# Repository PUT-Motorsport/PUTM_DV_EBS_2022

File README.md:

# PUTM_DV_EBS_2022
A KiCad schematic and PCB project of the Emergency Brake System circuit board.

NOTE: PCB project will be updated to match EBS_1.2 scheme.

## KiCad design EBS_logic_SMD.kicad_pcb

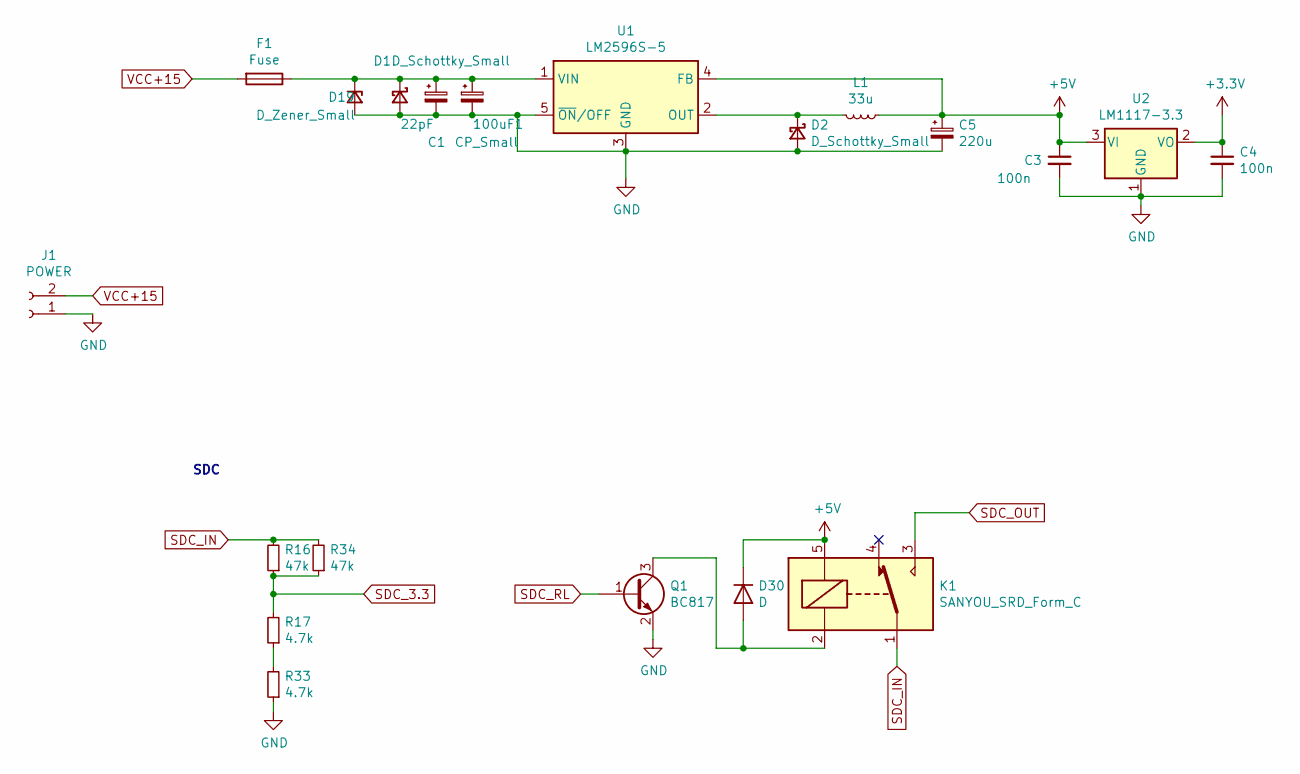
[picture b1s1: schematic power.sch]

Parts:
100uF1: CP_Small; C_1206_3216Metric
C1: 22pF; CP_Elec_6.3x5.8
C3, C4: 100n; C_1206_3216Metric
C5: 220u; CP_Elec_6.3x5.8
D1, D2: D_Schottky_Small; D_SMB
D19: D_Zener_Small; D_SMB
D30: D; D_SMB
F1: Fuse; D_SMB
J1: POWER; Molex_Micro-Fit_3.0_43650-0200_1x02_P3.00mm_Horizontal
K1: SANYOU_SRD_Form_C; Relay_SPDT_SANYOU_SRD_Series_Form_C
L1: 33u; L_12x12mm_H8mm
Q1: BC817; SOT-23
R16, R34: 47k; R_1206_3216Metric
R17, R33: 4.7k; R_1206_3216Metric
U1: LM2596S-5; TO-263-5_TabPin3
U2: LM1117-3.3; SOT-223

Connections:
+5V: C3.1, C5.1, D30.1 (K), K1.5, L1.1, U1.4 (FB), U2.3 (VI); also elsewhere on the board
GND: 100uF1.2, C1.2, C3.2, C4.2, C5.2, D1.2 (A), D2.2 (A), D19.2 (A), J1.1, Q1.2 (E), R33.1, U1.3 (GND), U1.5 (~ON~/OFF), U2.1 (GND); also elsewhere on the board
unnamed: 100uF1.1, C1.1, D1.1 (K), D19.1 (K), F1.1, U1.1 (VIN)
unnamed: D2.1 (K), L1.2, U1.2 (OUT)
unnamed: D30.2 (A), K1.2, Q1.3 (C)
unnamed: R17.1, R33.2
SDC_3.3: R16.1, R17.2, R34.1; also elsewhere on the board
SDC_IN: K1.1, R16.2, R34.2; also elsewhere on the board
SDC_OUT: K1.3; also elsewhere on the board
SDC_RL: Q1.1 (B); also elsewhere on the board
VCC: C4.1, U2.2 (VO); also elsewhere on the board
VCC+15: F1.2, J1.2

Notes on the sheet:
SDC

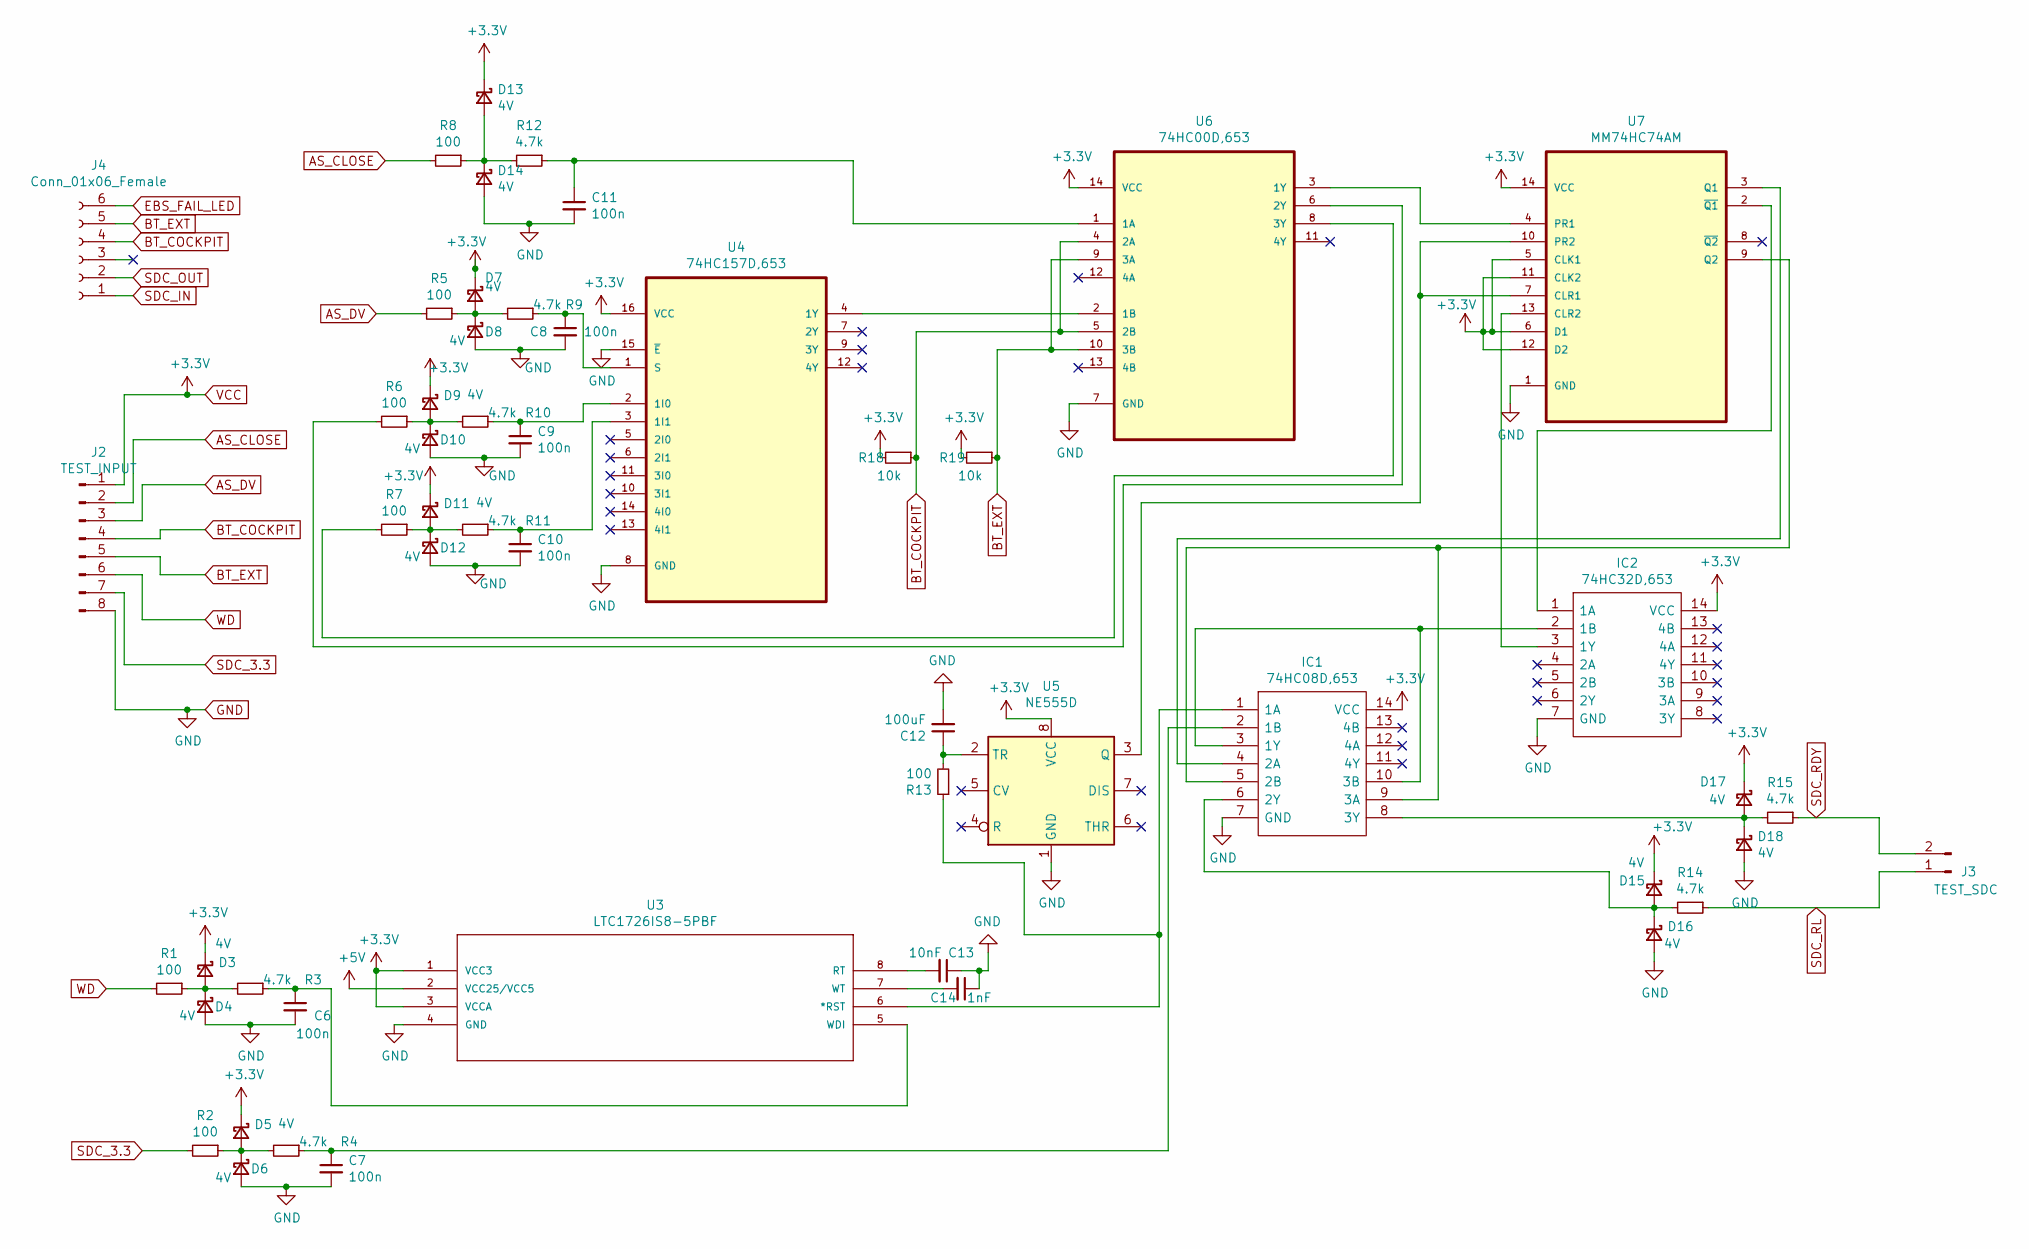
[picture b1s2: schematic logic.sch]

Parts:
C6, C7, C8, C9, C10, C11: 100n; C_1206_3216Metric
C12: 100uF; C_1206_3216Metric
C13: 10nF; C_1206_3216Metric
C14: 1nF; C_1206_3216Metric
D3, D4, D5, D6, D7, D8, D9, D10, D11, D12, D13, D14, D15, D16, D17, D18: 4V; D_SOD-323
IC1: 74HC08D,653; SOIC127P600X175-14N; Mouser Part Number 771-74HC08D-T
IC2: 74HC32D,653; SOIC127P600X175-14N; Mouser Part Number 771-74HC32D-T
J2: TEST_INPUT; PinHeader_1x08_P2.54mm_Vertical
J3: TEST_SDC; PinHeader_1x02_P2.54mm_Vertical
J4: Conn_01x06_Female; Molex_Micro-Fit_3.0_43650-0600_1x06_P3.00mm_Horizontal
R1, R2, R5, R6, R7, R8, R13: 100; R_1206_3216Metric
R3, R4, R9, R10, R11, R12, R14, R15: 4.7k; R_1206_3216Metric
R18, R19: 10k; R_1206_3216Metric
U3: LTC1726IS8-5PBF; SO-8_S; MANUFACTURER_PART_NUMBER ltc1726is85#pbf
U4: 74HC157D,653; SOIC127P600X175-16N; MPN 74HC157D,653
U5: NE555D; SOIC-8_3.9x4.9mm_P1.27mm
U6: 74HC00D,653; SOIC127P600X175-14N; MPN 74HC00D,653
U7: MM74HC74AM; SOIC127P600X175-14N; MPN MM74HC74AM

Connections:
+5V: U3.2 (VCC25/VCC5); also elsewhere on the board
AS_CLOSE: J2.2, R8.2; also elsewhere on the board
AS_DV: J2.3, R5.2; also elsewhere on the board
BT_COCKPIT: J2.4, J4.4, R18.1, U6.4 (2A), U6.5 (2B)
BT_EXT: J2.5, J4.5, R19.1, U6.9 (3A), U6.10 (3B)
EBS_FAIL_LED: J4.6; also elsewhere on the board
GND: C6.2, C7.2, C8.2, C9.2, C10.2, C11.2, C12.2, C13.1, C14.1, D4.2 (A), D6.2 (A), D8.2 (A), D10.2 (A), D12.2 (A), D14.2 (A), D16.2 (A), D18.2 (A), IC1.7 (GND), IC2.7 (GND), J2.8, U3.4 (GND), U4.8 (GND), U4.15 (~E), U5.1 (GND), U6.7 (GND), U7.1 (GND); also elsewhere on the board
unnamed: C6.1, R3.1, U3.5 (WDI)
unnamed: C7.1, IC1.2 (1B), R4.1
unnamed: C8.1, R9.1, U4.1 (S)
unnamed: C9.1, R10.1, U4.2 (1I0)
unnamed: C10.1, R11.1, U4.3 (1I1)
unnamed: C11.1, R12.1, U6.1 (1A)
unnamed: C12.1, R13.2, U5.2 (TR)
unnamed: C13.2, U3.8 (RT)
unnamed: C14.2, U3.7 (WT)
unnamed: D3.2 (A), D4.1 (K), R1.1, R3.2
unnamed: D5.2 (A), D6.1 (K), R2.1, R4.2
unnamed: D7.2 (A), D8.1 (K), R5.1, R9.2
unnamed: D9.2 (A), D10.1 (K), R6.1, R10.2
unnamed: D11.2 (A), D12.1 (K), R7.1, R11.2
unnamed: D13.2 (A), D14.1 (K), R8.1, R12.2
unnamed: D15.2 (A), D16.1 (K), IC1.6 (2Y), R14.2
unnamed: D17.2 (A), D18.1 (K), IC1.8 (3Y), R15.2
unnamed: IC1.1 (1A), R13.1, U3.6 (*RST)
unnamed: IC1.4 (2A), U7.3 (Q1)
unnamed: IC1.5 (2B), IC1.9 (3A), U7.9 (Q2)
unnamed: IC1.3 (1Y), IC1.10 (3B), IC2.2 (1B)
unnamed: IC2.1 (1A), U7.2 (~Q1)
unnamed: IC2.3 (1Y), U7.13 (CLR2)
unnamed: R6.2, U6.6 (2Y)
unnamed: R7.2, U6.8 (3Y)
unnamed: U4.4 (1Y), U6.2 (1B)
unnamed: U5.3 (Q), U7.7 (CLR1), U7.10 (PR2)
unnamed: U6.3 (1Y), U7.4 (PR1)
SDC_3.3: J2.7, R2.2; also elsewhere on the board
SDC_IN: J4.1; also elsewhere on the board
SDC_OUT: J4.2; also elsewhere on the board
SDC_RDY: J3.2, R15.1; also elsewhere on the board
SDC_RL: J3.1, R14.1; also elsewhere on the board
VCC: D3.1 (K), D5.1 (K), D7.1 (K), D9.1 (K), D11.1 (K), D13.1 (K), D15.1 (K), D17.1 (K), IC1.14 (VCC), IC2.14 (VCC), J2.1, R18.2, R19.2, U3.1 (VCC3), U3.3 (VCCA), U4.16 (VCC), U5.8 (VCC), U6.14 (VCC), U7.5 (CLK1), U7.6 (D1), U7.11 (CLK2), U7.12 (D2), U7.14 (VCC); also elsewhere on the board
WD: J2.6, R1.2; also elsewhere on the board

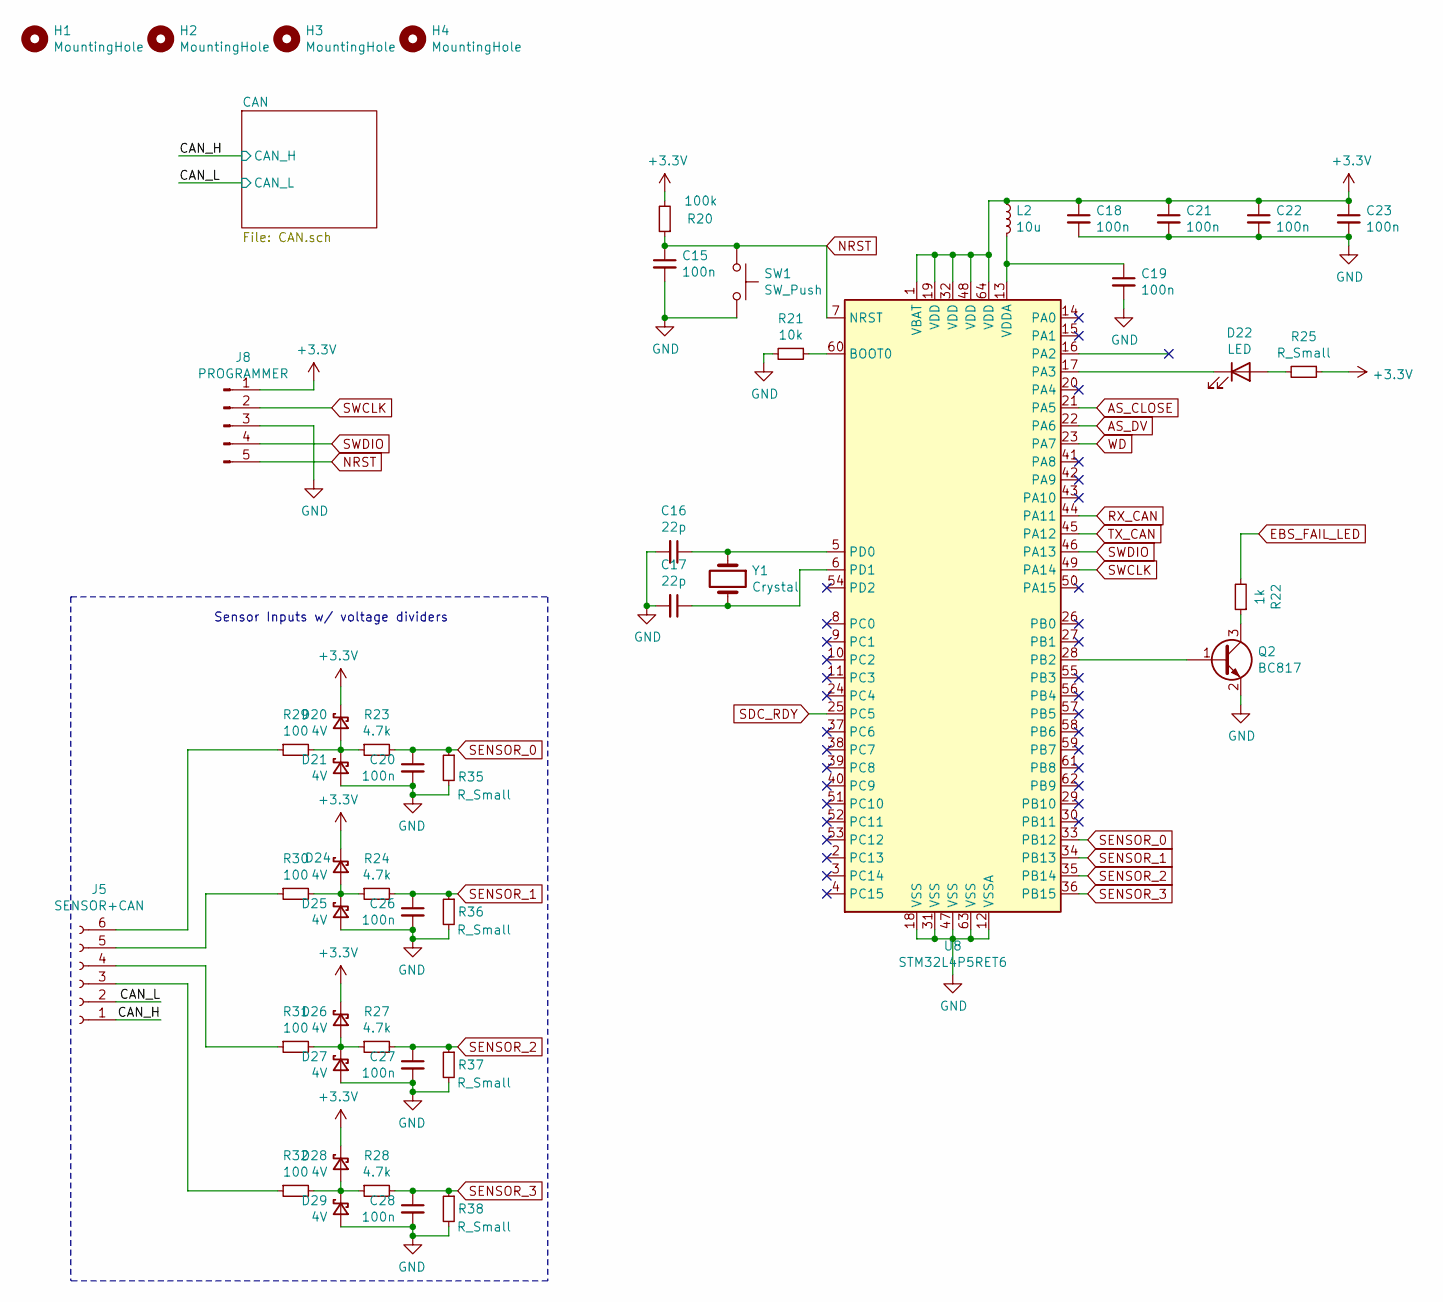
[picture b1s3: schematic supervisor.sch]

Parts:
C15, C18, C19, C20, C21, C22, C23, C26, C27, C28: 100n; C_1206_3216Metric
C16, C17: 22p; C_1206_3216Metric
D20, D21, D24, D25, D26, D27, D28, D29: 4V; D_SOD-323
D22: LED; D_SMB
H1, H2, H3, H4: MountingHole; MountingHole_3.2mm_M3
J5: SENSOR+CAN; Molex_Micro-Fit_3.0_43650-0600_1x06_P3.00mm_Horizontal
J8: PROGRAMMER; PinHeader_1x05_P2.54mm_Vertical
L2: 10u; L_2816_7142Metric_Pad3.20x4.45mm_HandSolder
Q2: BC817; SOT-23
R20: 100k; R_1206_3216Metric
R21: 10k; R_1206_3216Metric
R22: 1k; R_1206_3216Metric
R23, R24, R27, R28: 4.7k; R_1206_3216Metric
R25, R35, R36, R37, R38: R_Small; R_1206_3216Metric
R29, R30, R31, R32: 100; R_1206_3216Metric
SW1: SW_Push; SW_PUSH_6mm
U8: STM32L4P5RET6; LQFP-64_10x10mm_P0.5mm
Y1: Crystal; Crystal_SMD_HC49-SD

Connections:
/supervisor/CAN_H: J5.1; also elsewhere on the board
/supervisor/CAN_L: J5.2; also elsewhere on the board
AS_CLOSE: U8.21 (PA5); also elsewhere on the board
AS_DV: U8.22 (PA6); also elsewhere on the board
EBS_FAIL_LED: R22.2; also elsewhere on the board
GND: C15.2, C16.2, C17.2, C18.2, C19.2, C20.2, C21.2, C22.2, C23.2, C26.2, C27.2, C28.2, D21.2 (A), D25.2 (A), D27.2 (A), D29.2 (A), J8.3, Q2.2 (E), R21.2, R35.2, R36.2, R37.2, R38.2, SW1.2, U8.12 (VSSA), U8.18 (VSS), U8.31 (VSS), U8.47 (VSS), U8.63 (VSS); also elsewhere on the board
NRST: C15.1, J8.5, R20.1, SW1.1, U8.7 (NRST)
unnamed: C16.1, U8.5 (PD0), Y1.1
unnamed: C17.1, U8.6 (PD1), Y1.2
unnamed: C19.1, L2.2, U8.13 (VDDA)
unnamed: D20.2 (A), D21.1 (K), R23.1, R29.2
unnamed: D22.1 (K), U8.17 (PA3)
unnamed: D22.2 (A), R25.2
unnamed: D24.2 (A), D25.1 (K), R24.1, R30.2
unnamed: D26.2 (A), D27.1 (K), R27.1, R31.2
unnamed: D28.2 (A), D29.1 (K), R28.1, R32.2
unnamed: J5.3, R32.1
unnamed: J5.4, R31.1
unnamed: J5.5, R30.1
unnamed: J5.6, R29.1
unnamed: Q2.1 (B), U8.28 (PB2)
unnamed: Q2.3 (C), R22.1
unnamed: R21.1, U8.60 (BOOT0)
RX_CAN: U8.44 (PA11); also elsewhere on the board
SDC_RDY: U8.25 (PC5); also elsewhere on the board
SENSOR_0: C20.1, R23.2, R35.1, U8.33 (PB12)
SENSOR_1: C26.1, R24.2, R36.1, U8.34 (PB13)
SENSOR_2: C27.1, R27.2, R37.1, U8.35 (PB14)
SENSOR_3: C28.1, R28.2, R38.1, U8.36 (PB15)
SWCLK: J8.2, U8.49 (PA14)
SWDIO: J8.4, U8.46 (PA13)
TX_CAN: U8.45 (PA12); also elsewhere on the board
VCC: C18.1, C21.1, C22.1, C23.1, D20.1 (K), D24.1 (K), D26.1 (K), D28.1 (K), J8.1, L2.1, R20.2, R25.1, U8.1 (VBAT), U8.19 (VDD), U8.32 (VDD), U8.48 (VDD), U8.64 (VDD); also elsewhere on the board
WD: U8.23 (PA7); also elsewhere on the board

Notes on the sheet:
Sensor Inputs w/ voltage dividers

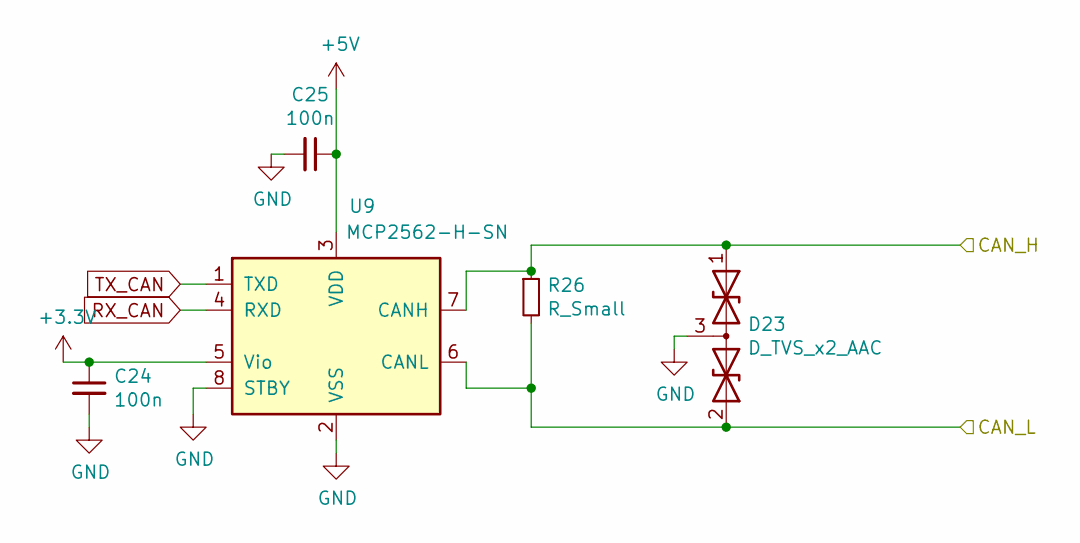
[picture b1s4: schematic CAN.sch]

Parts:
C24, C25: 100n; C_1206_3216Metric
D23: D_TVS_x2_AAC; SOT-23
R26: R_Small; R_1206_3216Metric
U9: MCP2562-H-SN; SOIC-8_3.9x4.9mm_P1.27mm

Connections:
+5V: C25.1, U9.3 (VDD); also elsewhere on the board
/supervisor/CAN_H: D23.1 (A1), R26.1, U9.7 (CANH); also elsewhere on the board
/supervisor/CAN_L: D23.2 (A2), R26.2, U9.6 (CANL); also elsewhere on the board
GND: C24.2, C25.2, D23.3 (common), U9.2 (VSS), U9.8 (STBY); also elsewhere on the board
RX_CAN: U9.4 (RXD); also elsewhere on the board
TX_CAN: U9.1 (TXD); also elsewhere on the board
VCC: C24.1, U9.5 (Vio); also elsewhere on the board

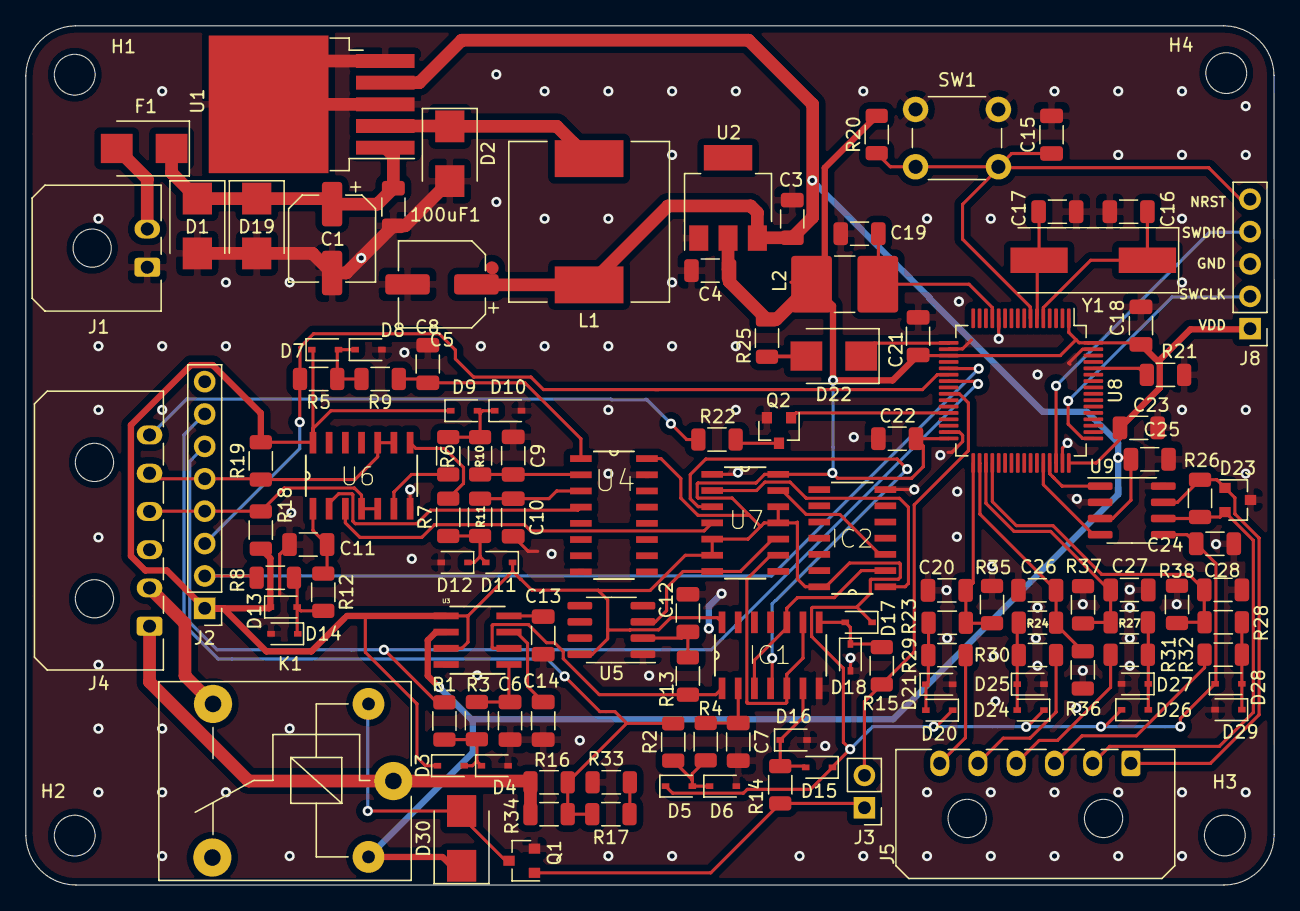
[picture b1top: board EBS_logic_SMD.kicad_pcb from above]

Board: 2 copper layers, 97.9 x 67.4 mm, 125 parts (0 on the bottom side), 74 nets.

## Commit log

2022-05-17 EBS 1.2 - scheme only
    Redesigned scheme for EBS logic board; PCB project yet to be updated.
